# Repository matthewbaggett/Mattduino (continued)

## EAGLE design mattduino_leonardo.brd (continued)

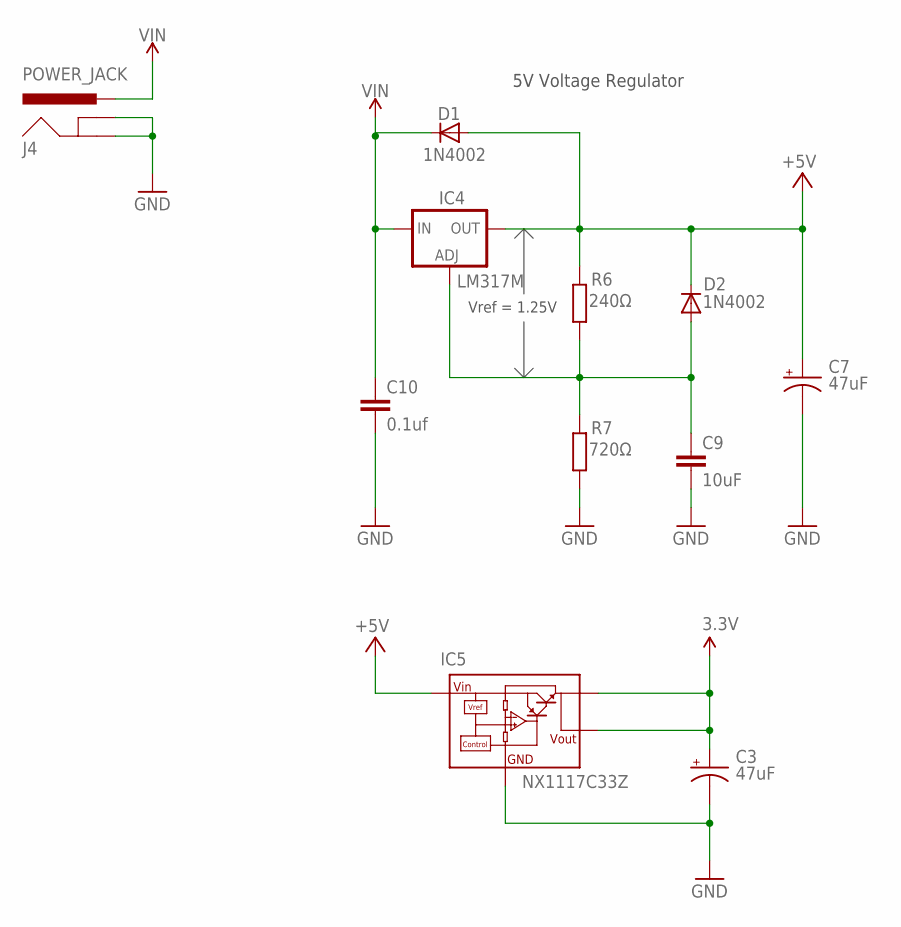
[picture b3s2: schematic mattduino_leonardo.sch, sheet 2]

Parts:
C3, C7: 47uF; PANASONIC_D
C9: 10uF; C1206
C10: 0.1uf; C1206
D1, D2: 1N4002; SOD-123
IC4: LM317MBSTT3; SOT223; PARTNUMBER LM317M
IC5: NX1117C33Z; SOT223
J4: POWER_JACK; POWER_JACK_PTH
R6: 240Ω; R1206
R7: 720Ω; R1206

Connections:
3.3V: C3.+, IC5.2 (VOUT1), IC5.4 (VOUT); also elsewhere on the board
+5V: C7.+, D1.A, D2.C, IC4.4 (OUT), IC5.3 (VIN), R6.2; also elsewhere on the board
GND: C3.-, C7.-, C9.2, C10.2, IC5.1 (GND), J4.GND, J4.GNDBREAK, R7.1; also elsewhere on the board
unnamed: C9.1, D2.A, IC4.1 (ADJ), R6.1, R7.2
VIN: C10.1, D1.C, IC4.3 (IN), J4.PWR; also elsewhere on the board

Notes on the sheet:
5V Voltage Regulator
Vref = 1.25V

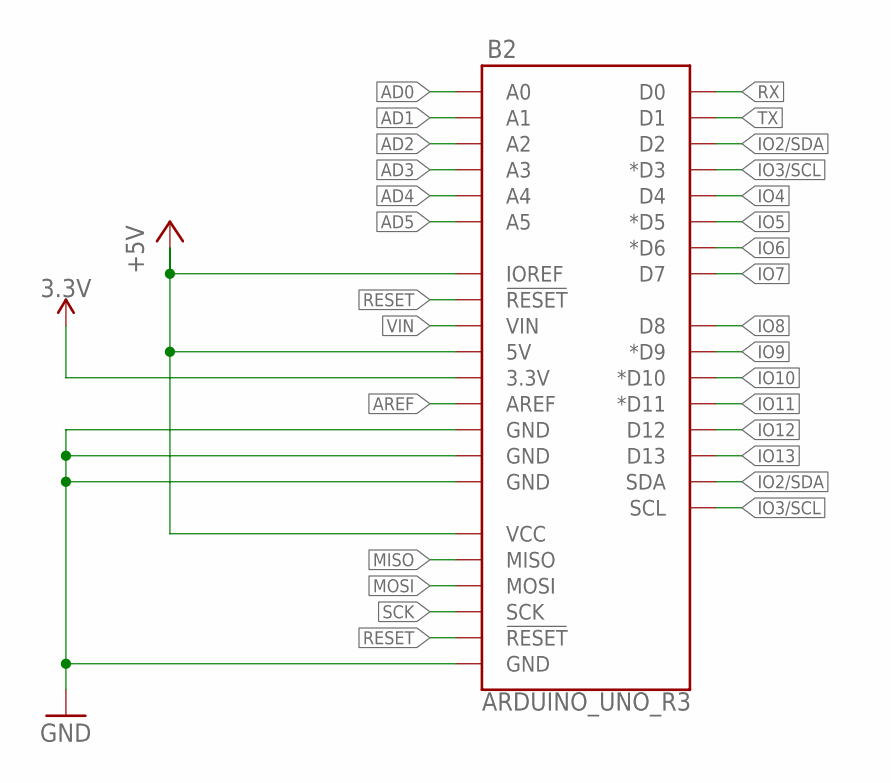
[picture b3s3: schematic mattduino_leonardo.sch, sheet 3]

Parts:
B2: ARDUINO_UNO_R3; ARDUINO_R3

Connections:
3.3V: B2.3.3V; also elsewhere on the board
+5V: B2.5V, B2.IOREF, B2.VCC; also elsewhere on the board
AD0: B2.A0; also elsewhere on the board
AD1: B2.A1; also elsewhere on the board
AD2: B2.A2; also elsewhere on the board
AD3: B2.A3; also elsewhere on the board
AD4: B2.A4; also elsewhere on the board
AD5: B2.A5; also elsewhere on the board
AREF: B2.AREF; also elsewhere on the board
GND: B2.GND@1 (GND), B2.GND@2 (GND), B2.GND@3 (GND), B2.GND@4 (GND); also elsewhere on the board
IO2/SDA: B2.D2, B2.SDA; also elsewhere on the board
IO3/SCL: B2.D3 (*D3), B2.SCL; also elsewhere on the board
IO4: B2.D4; also elsewhere on the board
IO5: B2.D5 (*D5); also elsewhere on the board
IO6: B2.D6 (*D6); also elsewhere on the board
IO7: B2.D7; also elsewhere on the board
IO8: B2.D8; also elsewhere on the board
IO9: B2.D9 (*D9); also elsewhere on the board
IO10: B2.D10 (*D10); also elsewhere on the board
IO11: B2.D11 (*D11); also elsewhere on the board
IO12: B2.D12; also elsewhere on the board
IO13: B2.D13; also elsewhere on the board
MISO: B2.MISO; also elsewhere on the board
MOSI: B2.MOSI; also elsewhere on the board
RESET: B2.RESET@1 (!RESET!), B2.RESET@2 (!RESET!); also elsewhere on the board
RX: B2.D0; also elsewhere on the board
SCK: B2.SCK; also elsewhere on the board
TX: B2.D1; also elsewhere on the board
VIN: B2.VIN; also elsewhere on the board

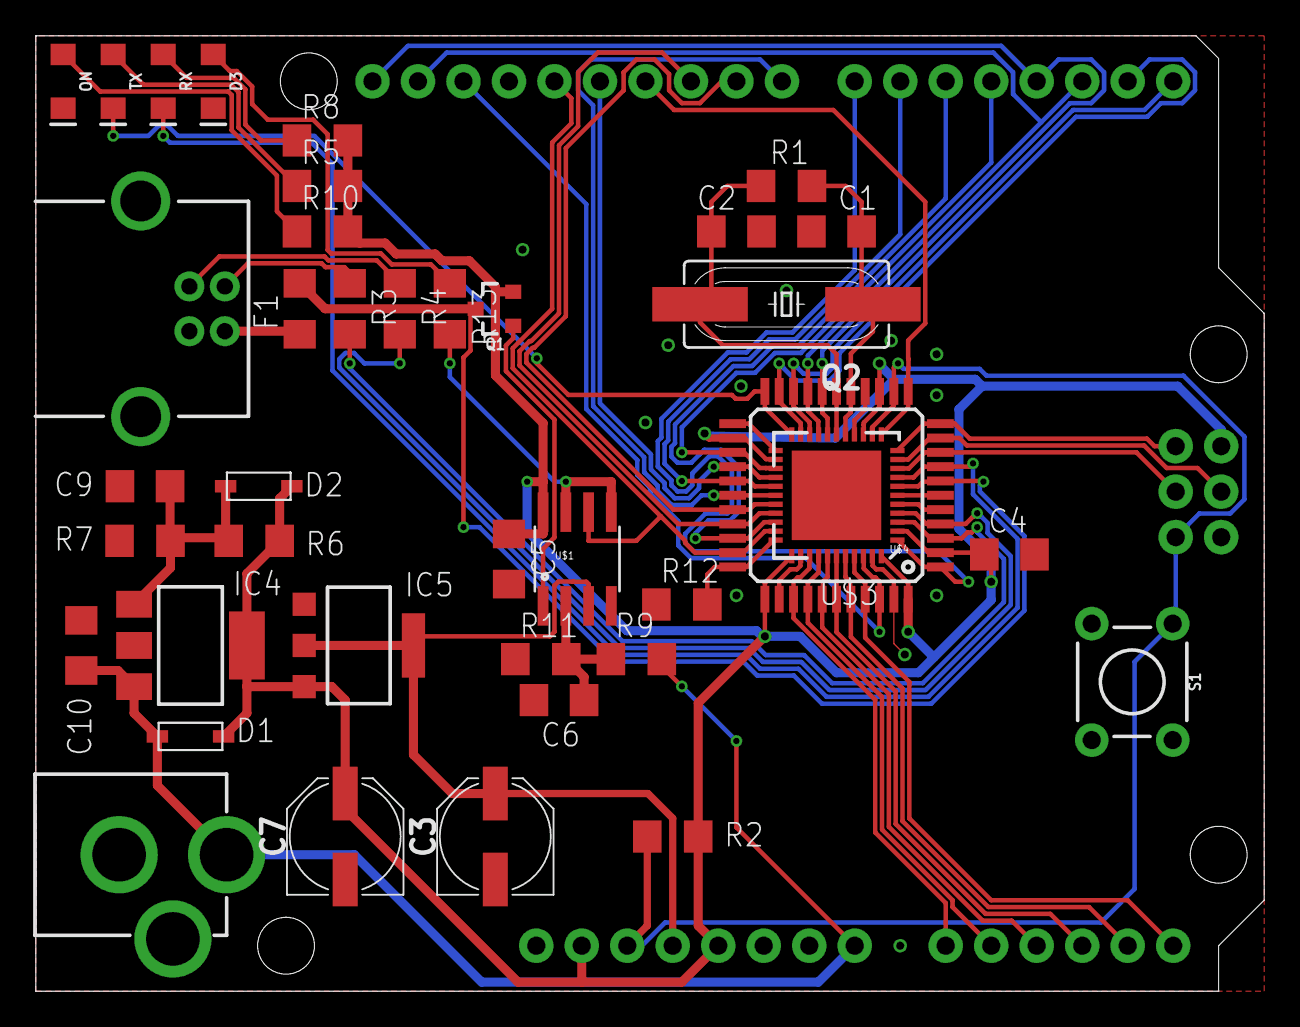
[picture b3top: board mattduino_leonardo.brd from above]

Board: 2 copper layers, 68.6 x 53.3 mm, 40 parts (0 on the bottom side), 48 nets.

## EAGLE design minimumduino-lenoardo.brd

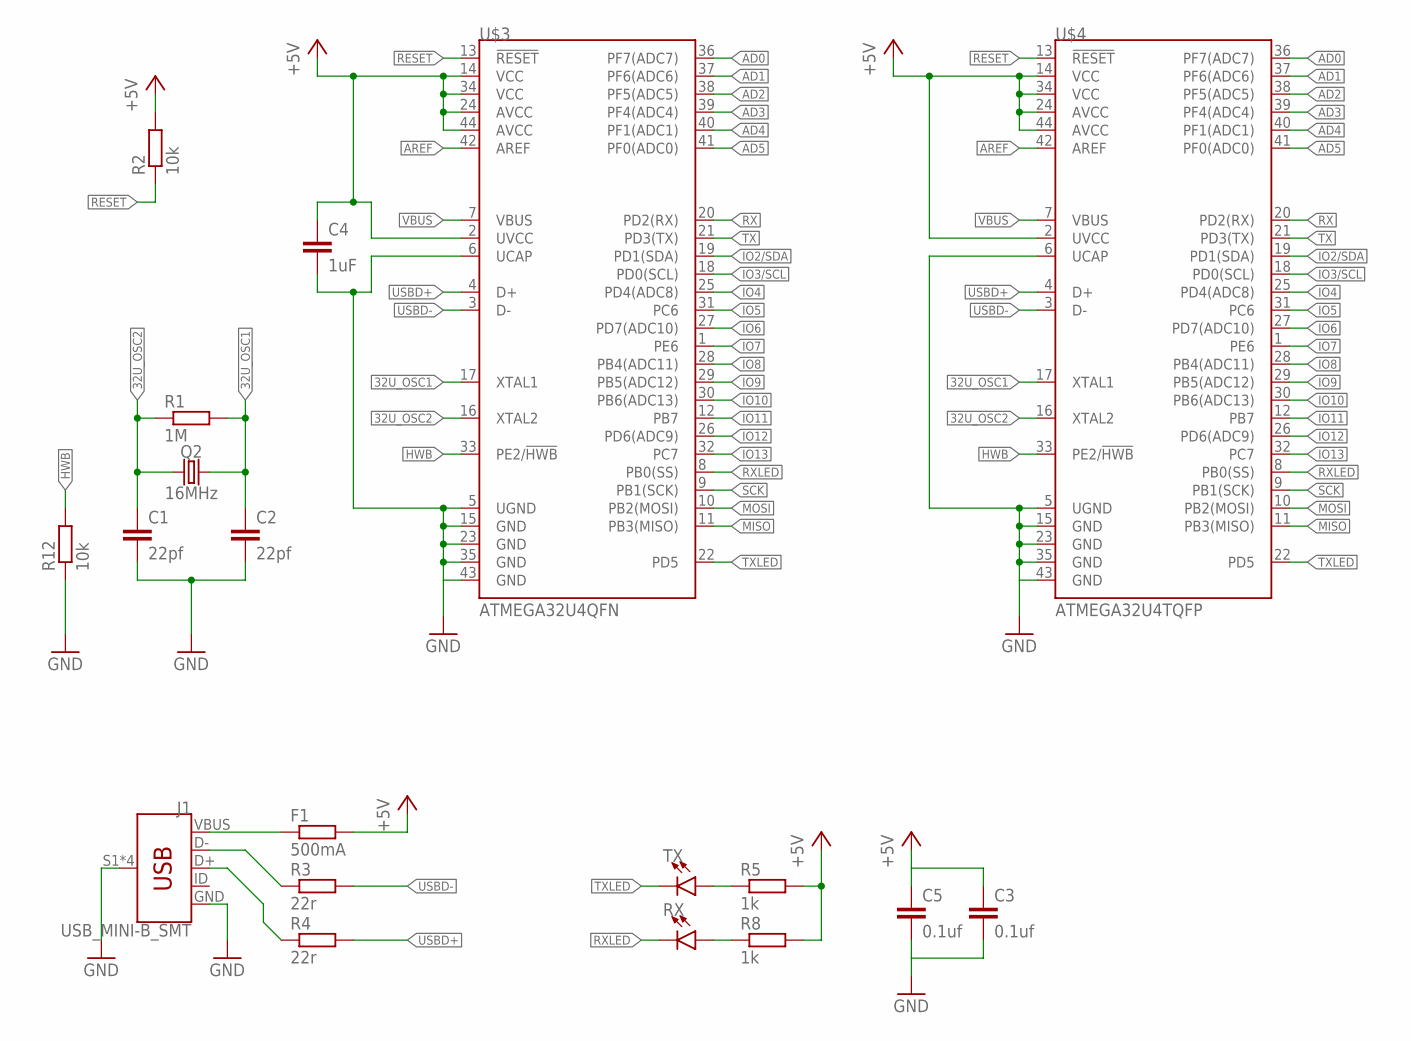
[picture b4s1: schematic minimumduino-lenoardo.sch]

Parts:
C1, C2: 22pf; C0805
C3, C5: 0.1uf; C0805
C4: 1uF; C0805
F1: 500mA; R1206
J1: USB_MINI-B_SMT; USB-MINIB
Q2: 16MHz; CRYSTAL-SMD-5X3.2-4PAD
R1: 1M; R0805
R2, R12: 10k; R0805
R3, R4: 22r; R0805
R5, R8: 1k; R0805
RX: LED1206; LED-1206
TX: LED1206; LED-1206
U$3: ATMEGA32U4QFN; SPARKFUN-DIGITALIC_QFN-44
U$4: ATMEGA32U4TQFP; SPARKFUN-DIGITALIC_TQFP44

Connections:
32U_OSC1: C2.1, Q2.3 (2), R1.2, U$3.17 (XTAL1), U$4.17 (XTAL1)
32U_OSC2: C1.1, Q2.1, R1.1, U$3.16 (XTAL2), U$4.16 (XTAL2)
+5V: C3.1, C4.1, C5.1, F1.2, R2.2, R5.2, R8.2, U$3.2 (UVCC), U$3.14 (VCC), U$3.24 (AVCC), U$3.34 (VCC), U$3.44 (AVCC), U$4.2 (UVCC), U$4.14 (VCC), U$4.24 (AVCC), U$4.34 (VCC), U$4.44 (AVCC)
AD0: U$3.36 (PF7(ADC7)), U$4.36 (PF7(ADC7))
AD1: U$3.37 (PF6(ADC6)), U$4.37 (PF6(ADC6))
AD2: U$3.38 (PF5(ADC5)), U$4.38 (PF5(ADC5))
AD3: U$3.39 (PF4(ADC4)), U$4.39 (PF4(ADC4))
AD4: U$3.40 (PF1(ADC1)), U$4.40 (PF1(ADC1))
AD5: U$3.41 (PF0(ADC0)), U$4.41 (PF0(ADC0))
AREF: U$3.42 (AREF), U$4.42 (AREF)
GND: C1.2, C2.2, C3.2, C4.2, C5.2, J1.GND, J1.S1 (SHIELD), J1.S2 (SHIELD), J1.S3 (SHIELD), J1.S4 (SHIELD), R12.1, U$3.5 (UGND), U$3.6 (UCAP), U$3.15 (GND), U$3.23 (GND), U$3.35 (GND), U$3.43 (GND), U$4.5 (UGND), U$4.6 (UCAP), U$4.15 (GND), U$4.23 (GND), U$4.35 (GND), U$4.43 (GND)
HWB: R12.2, U$3.33 (PE2/!HWB), U$4.33 (PE2/!HWB)
IO2/SDA: U$3.19 (PD1(SDA)), U$4.19 (PD1(SDA))
IO3/SCL: U$3.18 (PD0(SCL)), U$4.18 (PD0(SCL))
IO4: U$3.25 (PD4(ADC8)), U$4.25 (PD4(ADC8))
IO5: U$3.31 (PC6), U$4.31 (PC6)
IO6: U$3.27 (PD7(ADC10)), U$4.27 (PD7(ADC10))
IO7: U$3.1 (PE6), U$4.1 (PE6)
IO8: U$3.28 (PB4(ADC11)), U$4.28 (PB4(ADC11))
IO9: U$3.29 (PB5(ADC12)), U$4.29 (PB5(ADC12))
IO10: U$3.30 (PB6(ADC13)), U$4.30 (PB6(ADC13))
IO11: U$3.12 (PB7), U$4.12 (PB7)
IO12: U$3.26 (PD6(ADC9)), U$4.26 (PD6(ADC9))
IO13: U$3.32 (PC7), U$4.32 (PC7)
MISO: U$3.11 (PB3(MISO)), U$4.11 (PB3(MISO))
MOSI: U$3.10 (PB2(MOSI)), U$4.10 (PB2(MOSI))
unnamed: R8.1, RX.A
unnamed: R5.1, TX.A
RESET: R2.1, U$3.13 (!RESET), U$4.13 (!RESET)
RX: U$3.20 (PD2(RX)), U$4.20 (PD2(RX))
RXLED: RX.C, U$3.8 (PB0(SS)), U$4.8 (PB0(SS))
SCK: U$3.9 (PB1(SCK)), U$4.9 (PB1(SCK))
TX: U$3.21 (PD3(TX)), U$4.21 (PD3(TX))
TXLED: TX.C, U$3.22 (PD5), U$4.22 (PD5)
USBD+: R4.2, U$3.4 (D+), U$4.4 (D+)
USBD-: R3.2, U$3.3 (D-), U$4.3 (D-)
USBR+: J1.D+, R4.1
USBR-: J1.D-, R3.1
VBUS: U$3.7 (VBUS), U$4.7 (VBUS)
VBUS_UNFUSED: F1.1, J1.VBUS

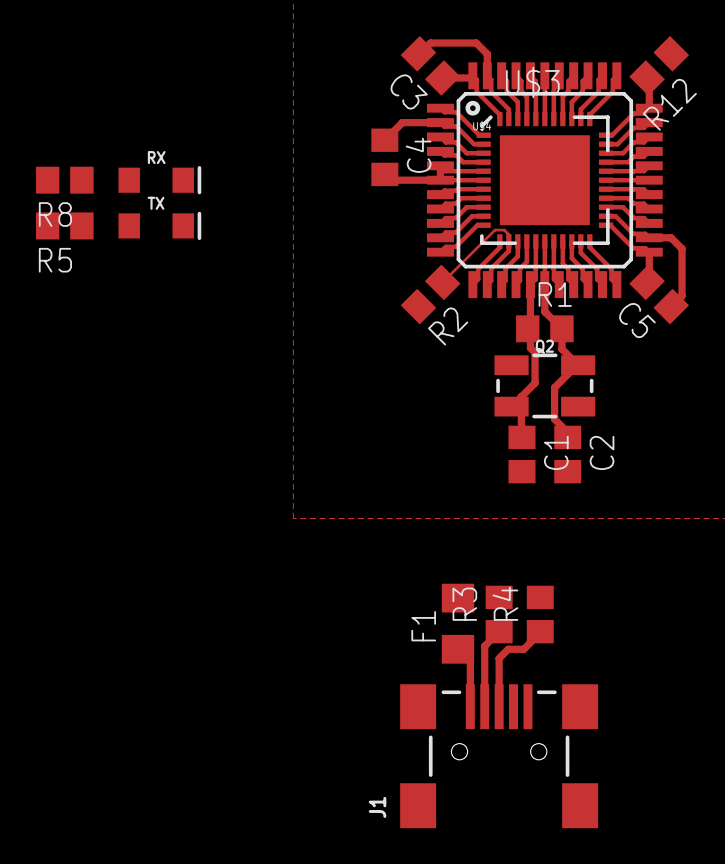
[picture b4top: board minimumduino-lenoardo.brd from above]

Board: 2 copper layers, 19 parts (0 on the bottom side), 40 nets.

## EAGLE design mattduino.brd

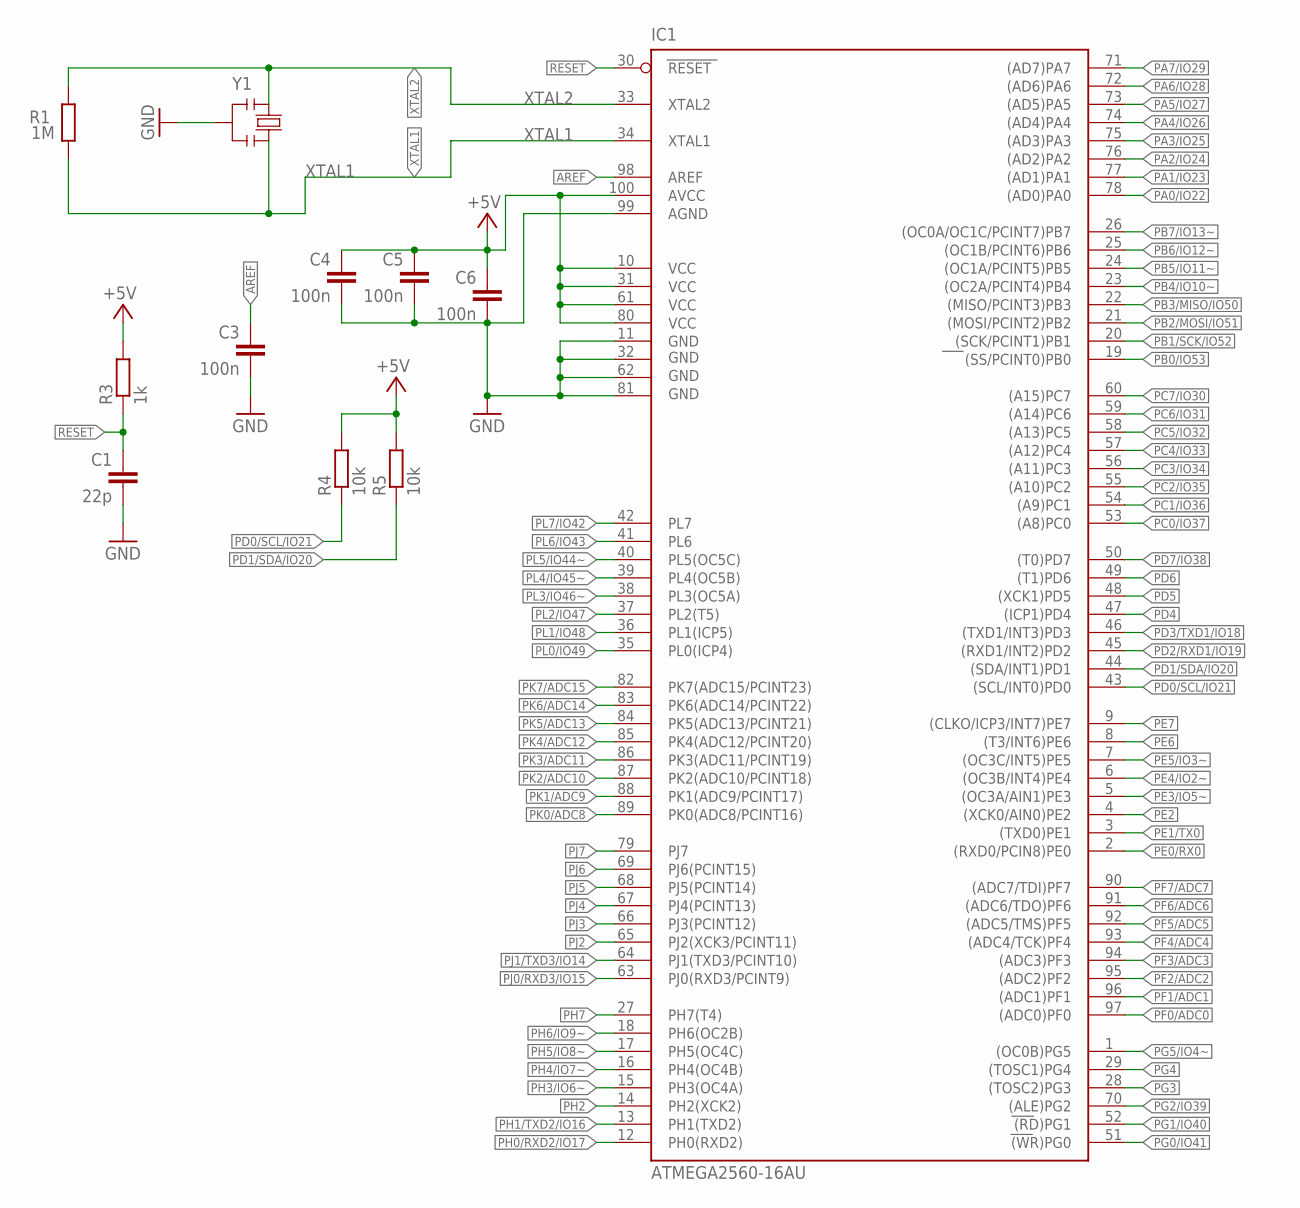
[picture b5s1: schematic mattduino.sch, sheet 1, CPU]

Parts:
C1: 22p; C1206
C3, C4, C5, C6: 100n; C1206
IC1: ATMEGA2560-16AU; TQFP100
R1: 1M; R1206
R3: 1k; R1206
R4, R5: 10k; R1206
Y1: CSTCE16M0V53-R0 16MHZ; RESONATOR

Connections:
+5V: C4.1, C5.1, C6.1, IC1.10 (VCC), IC1.31 (VCC1), IC1.61 (VCC2), IC1.80 (VCC3), IC1.100 (AVCC), R3.2, R4.2, R5.2; also elsewhere on the board
AREF: C3.1, IC1.98 (AREF); also elsewhere on the board
GND: C1.2, C3.2, C4.2, C5.2, C6.2, IC1.11 (GND), IC1.32 (GND1), IC1.62 (GND2), IC1.81 (GND3), IC1.99 (AGND), Y1.2; also elsewhere on the board
PA0/IO22: IC1.78 ((AD0)PA0); also elsewhere on the board
PA1/IO23: IC1.77 ((AD1)PA1); also elsewhere on the board
PA2/IO24: IC1.76 ((AD2)PA2); also elsewhere on the board
PA3/IO25: IC1.75 ((AD3)PA3); also elsewhere on the board
PA4/IO26: IC1.74 ((AD4)PA4); also elsewhere on the board
PA5/IO27: IC1.73 ((AD5)PA5); also elsewhere on the board
PA6/IO28: IC1.72 ((AD6)PA6); also elsewhere on the board
PA7/IO29: IC1.71 ((AD7)PA7); also elsewhere on the board
PB0/IO53: IC1.19 ((SS/PCINT0)PB0); also elsewhere on the board
PB1/SCK/IO52: IC1.20 ((SCK/PCINT1)PB1); also elsewhere on the board
PB2/MOSI/IO51: IC1.21 ((MOSI/PCINT2)PB2); also elsewhere on the board
PB3/MISO/IO50: IC1.22 ((MISO/PCINT3)PB3); also elsewhere on the board
PB4/IO10~: IC1.23 ((OC2A/PCINT4)PB4); also elsewhere on the board
PB5/IO11~: IC1.24 ((OC1A/PCINT5)PB5); also elsewhere on the board
PB6/IO12~: IC1.25 ((OC1B/PCINT6)PB6); also elsewhere on the board
PB7/IO13~: IC1.26 ((OC0A/OC1C/PCINT7)PB7); also elsewhere on the board
PC0/IO37: IC1.53 ((A8)PC0); also elsewhere on the board
PC1/IO36: IC1.54 ((A9)PC1); also elsewhere on the board
PC2/IO35: IC1.55 ((A10)PC2); also elsewhere on the board
PC3/IO34: IC1.56 ((A11)PC3); also elsewhere on the board
PC4/IO33: IC1.57 ((A12)PC4); also elsewhere on the board
PC5/IO32: IC1.58 ((A13)PC5); also elsewhere on the board
PC6/IO31: IC1.59 ((A14)PC6); also elsewhere on the board
PC7/IO30: IC1.60 ((A15)PC7); also elsewhere on the board
PD0/SCL/IO21: IC1.43 ((SCL/INT0)PD0), R4.1; also elsewhere on the board
PD1/SDA/IO20: IC1.44 ((SDA/INT1)PD1), R5.1; also elsewhere on the board
PD2/RXD1/IO19: IC1.45 ((RXD1/INT2)PD2); also elsewhere on the board
PD3/TXD1/IO18: IC1.46 ((TXD1/INT3)PD3); also elsewhere on the board
PD4: IC1.47 ((ICP1)PD4); also elsewhere on the board
PD5: IC1.48 ((XCK1)PD5); also elsewhere on the board
PD6: IC1.49 ((T1)PD6); also elsewhere on the board
PD7/IO38: IC1.50 ((T0)PD7); also elsewhere on the board
PE0/RX0: IC1.2 ((RXD0/PCIN8)PE0); also elsewhere on the board
PE1/TX0: IC1.3 ((TXD0)PE1); also elsewhere on the board
PE2: IC1.4 ((XCK0/AIN0)PE2); also elsewhere on the board
PE3/IO5~: IC1.5 ((OC3A/AIN1)PE3); also elsewhere on the board
PE4/IO2~: IC1.6 ((OC3B/INT4)PE4); also elsewhere on the board
PE5/IO3~: IC1.7 ((OC3C/INT5)PE5); also elsewhere on the board
PE6: IC1.8 ((T3/INT6)PE6); also elsewhere on the board
PE7: IC1.9 ((CLKO/ICP3/INT7)PE7); also elsewhere on the board
PF0/ADC0: IC1.97 ((ADC0)PF0); also elsewhere on the board
PF1/ADC1: IC1.96 ((ADC1)PF1); also elsewhere on the board
PF2/ADC2: IC1.95 ((ADC2)PF2); also elsewhere on the board
PF3/ADC3: IC1.94 ((ADC3)PF3); also elsewhere on the board
PF4/ADC4: IC1.93 ((ADC4/TCK)PF4); also elsewhere on the board
PF5/ADC5: IC1.92 ((ADC5/TMS)PF5); also elsewhere on the board
PF6/ADC6: IC1.91 ((ADC6/TDO)PF6); also elsewhere on the board
PF7/ADC7: IC1.90 ((ADC7/TDI)PF7); also elsewhere on the board
PG0/IO41: IC1.51 ((WR)PG0); also elsewhere on the board
PG1/IO40: IC1.52 ((RD)PG1); also elsewhere on the board
PG2/IO39: IC1.70 ((ALE)PG2); also elsewhere on the board
PG3: IC1.28 ((TOSC2)PG3); also elsewhere on the board
PG4: IC1.29 ((TOSC1)PG4); also elsewhere on the board
PG5/IO4~: IC1.1 ((OC0B)PG5); also elsewhere on the board
PH0/RXD2/IO17: IC1.12 (PH0(RXD2)); also elsewhere on the board
PH1/TXD2/IO16: IC1.13 (PH1(TXD2)); also elsewhere on the board
PH2: IC1.14 (PH2(XCK2)); also elsewhere on the board
PH3/IO6~: IC1.15 (PH3(OC4A)); also elsewhere on the board
PH4/IO7~: IC1.16 (PH4(OC4B)); also elsewhere on the board
PH5/IO8~: IC1.17 (PH5(OC4C)); also elsewhere on the board
PH6/IO9~: IC1.18 (PH6(OC2B)); also elsewhere on the board
PH7: IC1.27 (PH7(T4)); also elsewhere on the board
PJ0/RXD3/IO15: IC1.63 (PJ0(RXD3/PCINT9)); also elsewhere on the board
PJ1/TXD3/IO14: IC1.64 (PJ1(TXD3/PCINT10)); also elsewhere on the board
PJ2: IC1.65 (PJ2(XCK3/PCINT11)); also elsewhere on the board
PJ3: IC1.66 (PJ3(PCINT12)); also elsewhere on the board
PJ4: IC1.67 (PJ4(PCINT13)); also elsewhere on the board
PJ5: IC1.68 (PJ5(PCINT14)); also elsewhere on the board
PJ6: IC1.69 (PJ6(PCINT15)); also elsewhere on the board
PJ7: IC1.79 (PJ7); also elsewhere on the board
PK0/ADC8: IC1.89 (PK0(ADC8/PCINT16)); also elsewhere on the board
PK1/ADC9: IC1.88 (PK1(ADC9/PCINT17)); also elsewhere on the board
PK2/ADC10: IC1.87 (PK2(ADC10/PCINT18)); also elsewhere on the board
PK3/ADC11: IC1.86 (PK3(ADC11/PCINT19)); also elsewhere on the board
PK4/ADC12: IC1.85 (PK4(ADC12/PCINT20)); also elsewhere on the board
PK5/ADC13: IC1.84 (PK5(ADC13/PCINT21)); also elsewhere on the board
PK6/ADC14: IC1.83 (PK6(ADC14/PCINT22)); also elsewhere on the board
PK7/ADC15: IC1.82 (PK7(ADC15/PCINT23)); also elsewhere on the board
PL0/IO49: IC1.35 (PL0(ICP4)); also elsewhere on the board
PL1/IO48: IC1.36 (PL1(ICP5)); also elsewhere on the board
PL2/IO47: IC1.37 (PL2(T5)); also elsewhere on the board
PL3/IO46~: IC1.38 (PL3(OC5A)); also elsewhere on the board
PL4/IO45~: IC1.39 (PL4(OC5B)); also elsewhere on the board
PL5/IO44~: IC1.40 (PL5(OC5C)); also elsewhere on the board
PL6/IO43: IC1.41 (PL6); also elsewhere on the board
PL7/IO42: IC1.42 (PL7); also elsewhere on the board
RESET: C1.1, IC1.30 (RESET), R3.1; also elsewhere on the board
XTAL1: IC1.34 (XTAL1), R1.1, Y1.3
XTAL2: IC1.33 (XTAL2), R1.2, Y1.1

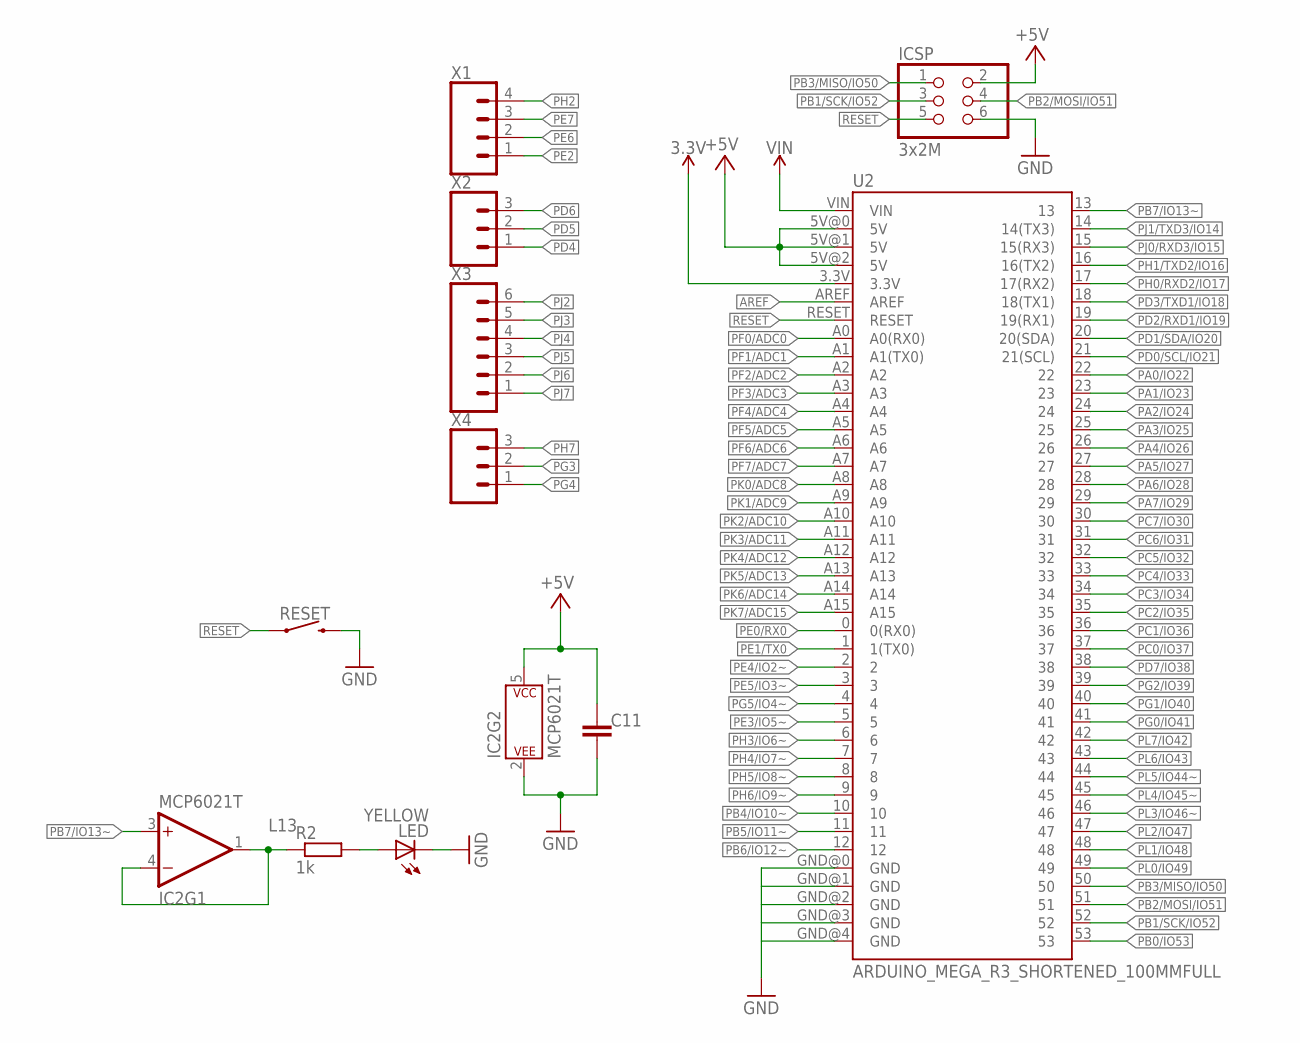
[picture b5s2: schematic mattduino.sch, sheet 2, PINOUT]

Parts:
C11: 100n; C1206
IC2: MCP6021T; SOT23-5
ICSP: 3x2M; 2X03
LED: YELLOW; CHIP-LED0805
R2: 1k; R1206
RESET: MOMENTARY-SWITCH-SPST-PTH-6.0MM; TACTILE_SWITCH_PTH_6.0MM
U2: ARDUINO_MEGA_R3_SHORTENED_100MMFULL; ARDUINO_MEGA_SHORTENED_100MM
X1: CONN_04; 1X04
X2, X4: CONN_03; 1X03
X3: CONN_06SILK_FEMALE_PTH; 1X06

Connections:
3.3V: U2.3.3V; also elsewhere on the board
+5V: C11.2, IC2.5 (P$V+), ICSP.2, U2.5V@0 (5V), U2.5V@1 (5V), U2.5V@2 (5V); also elsewhere on the board
AREF: U2.AREF; also elsewhere on the board
GND: C11.1, IC2.2 (P$V-), ICSP.6, LED.C, RESET.3 (2), U2.GND@0 (GND), U2.GND@1 (GND), U2.GND@2 (GND), U2.GND@3 (GND), U2.GND@4 (GND); also elsewhere on the board
L13: IC2.1 (OUT), IC2.4 (-IN), R2.1
unnamed: LED.A, R2.2
PA0/IO22: U2.22; also elsewhere on the board
PA1/IO23: U2.23; also elsewhere on the board
PA2/IO24: U2.24; also elsewhere on the board
PA3/IO25: U2.25; also elsewhere on the board
PA4/IO26: U2.26; also elsewhere on the board
PA5/IO27: U2.27; also elsewhere on the board
PA6/IO28: U2.28; also elsewhere on the board
PA7/IO29: U2.29; also elsewhere on the board
PB0/IO53: U2.53; also elsewhere on the board
PB1/SCK/IO52: ICSP.3, U2.52; also elsewhere on the board
PB2/MOSI/IO51: ICSP.4, U2.51; also elsewhere on the board
PB3/MISO/IO50: ICSP.1, U2.50; also elsewhere on the board
PB4/IO10~: U2.10; also elsewhere on the board
PB5/IO11~: U2.11; also elsewhere on the board
PB6/IO12~: U2.12; also elsewhere on the board
PB7/IO13~: IC2.3 (+IN), U2.13; also elsewhere on the board
PC0/IO37: U2.37; also elsewhere on the board
PC1/IO36: U2.36; also elsewhere on the board
PC2/IO35: U2.35; also elsewhere on the board
PC3/IO34: U2.34; also elsewhere on the board
PC4/IO33: U2.33; also elsewhere on the board
PC5/IO32: U2.32; also elsewhere on the board
PC6/IO31: U2.31; also elsewhere on the board
PC7/IO30: U2.30; also elsewhere on the board
PD0/SCL/IO21: U2.21 (21(SCL)); also elsewhere on the board
PD1/SDA/IO20: U2.20 (20(SDA)); also elsewhere on the board
PD2/RXD1/IO19: U2.19 (19(RX1)); also elsewhere on the board
PD3/TXD1/IO18: U2.18 (18(TX1)); also elsewhere on the board
PD4: X2.1; also elsewhere on the board
PD5: X2.2; also elsewhere on the board
PD6: X2.3; also elsewhere on the board
PD7/IO38: U2.38; also elsewhere on the board
PE0/RX0: U2.0 (0(RX0)); also elsewhere on the board
PE1/TX0: U2.1 (1(TX0)); also elsewhere on the board
PE2: X1.1; also elsewhere on the board
PE3/IO5~: U2.5; also elsewhere on the board
PE4/IO2~: U2.2; also elsewhere on the board
PE5/IO3~: U2.3; also elsewhere on the board
PE6: X1.2; also elsewhere on the board
PE7: X1.3; also elsewhere on the board
PF0/ADC0: U2.A0 (A0(RX0)); also elsewhere on the board
PF1/ADC1: U2.A1 (A1(TX0)); also elsewhere on the board
PF2/ADC2: U2.A2; also elsewhere on the board
PF3/ADC3: U2.A3; also elsewhere on the board
PF4/ADC4: U2.A4; also elsewhere on the board
PF5/ADC5: U2.A5; also elsewhere on the board
PF6/ADC6: U2.A6; also elsewhere on the board
PF7/ADC7: U2.A7; also elsewhere on the board
PG0/IO41: U2.41; also elsewhere on the board
PG1/IO40: U2.40; also elsewhere on the board
PG2/IO39: U2.39; also elsewhere on the board
PG3: X4.2; also elsewhere on the board
PG4: X4.1; also elsewhere on the board
PG5/IO4~: U2.4; also elsewhere on the board
PH0/RXD2/IO17: U2.17 (17(RX2)); also elsewhere on the board
PH1/TXD2/IO16: U2.16 (16(TX2)); also elsewhere on the board
PH2: X1.4; also elsewhere on the board
PH3/IO6~: U2.6; also elsewhere on the board
PH4/IO7~: U2.7; also elsewhere on the board
PH5/IO8~: U2.8; also elsewhere on the board
PH6/IO9~: U2.9; also elsewhere on the board
PH7: X4.3; also elsewhere on the board
PJ0/RXD3/IO15: U2.15 (15(RX3)); also elsewhere on the board
PJ1/TXD3/IO14: U2.14 (14(TX3)); also elsewhere on the board
PJ2: X3.6; also elsewhere on the board
PJ3: X3.5; also elsewhere on the board
PJ4: X3.4; also elsewhere on the board
PJ5: X3.3; also elsewhere on the board
PJ6: X3.2; also elsewhere on the board
PJ7: X3.1; also elsewhere on the board
PK0/ADC8: U2.A8; also elsewhere on the board
PK1/ADC9: U2.A9; also elsewhere on the board
PK2/ADC10: U2.A10; also elsewhere on the board
PK3/ADC11: U2.A11; also elsewhere on the board
PK4/ADC12: U2.A12; also elsewhere on the board
PK5/ADC13: U2.A13; also elsewhere on the board
PK6/ADC14: U2.A14; also elsewhere on the board
PK7/ADC15: U2.A15; also elsewhere on the board
PL0/IO49: U2.49; also elsewhere on the board
PL1/IO48: U2.48; also elsewhere on the board
PL2/IO47: U2.47; also elsewhere on the board
PL3/IO46~: U2.46; also elsewhere on the board
PL4/IO45~: U2.45; also elsewhere on the board
PL5/IO44~: U2.44; also elsewhere on the board
PL6/IO43: U2.43; also elsewhere on the board
PL7/IO42: U2.42; also elsewhere on the board
RESET: ICSP.5, RESET.1, U2.RESET; also elsewhere on the board
VIN: U2.VIN; also elsewhere on the board

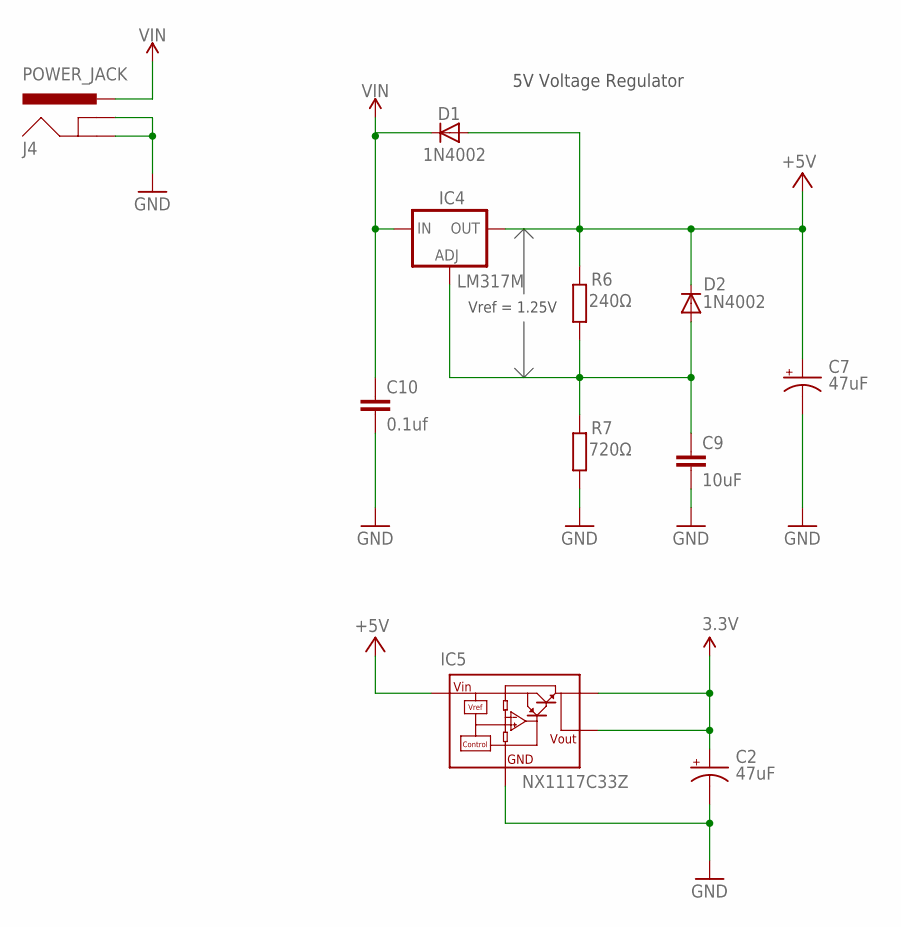
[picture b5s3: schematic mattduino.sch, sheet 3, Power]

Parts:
C2, C7: 47uF; PANASONIC_D
C9: 10uF; C1206
C10: 0.1uf; C1206
D1, D2: 1N4002; SOD-123
IC4: LM317MBSTT3; SOT223; PARTNUMBER LM317M
IC5: NX1117C33Z; SOT223
J4: POWER_JACK; POWER_JACK_PTH
R6: 240Ω; R1206
R7: 720Ω; R1206

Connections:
3.3V: C2.+, IC5.2 (VOUT1), IC5.4 (VOUT); also elsewhere on the board
+5V: C7.+, D1.A, D2.C, IC4.4 (OUT), IC5.3 (VIN), R6.2; also elsewhere on the board
GND: C2.-, C7.-, C9.2, C10.2, IC5.1 (GND), J4.GND, J4.GNDBREAK, R7.1; also elsewhere on the board
unnamed: C9.1, D2.A, IC4.1 (ADJ), R6.1, R7.2
VIN: C10.1, D1.C, IC4.3 (IN), J4.PWR; also elsewhere on the board

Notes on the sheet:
5V Voltage Regulator
Vref = 1.25V

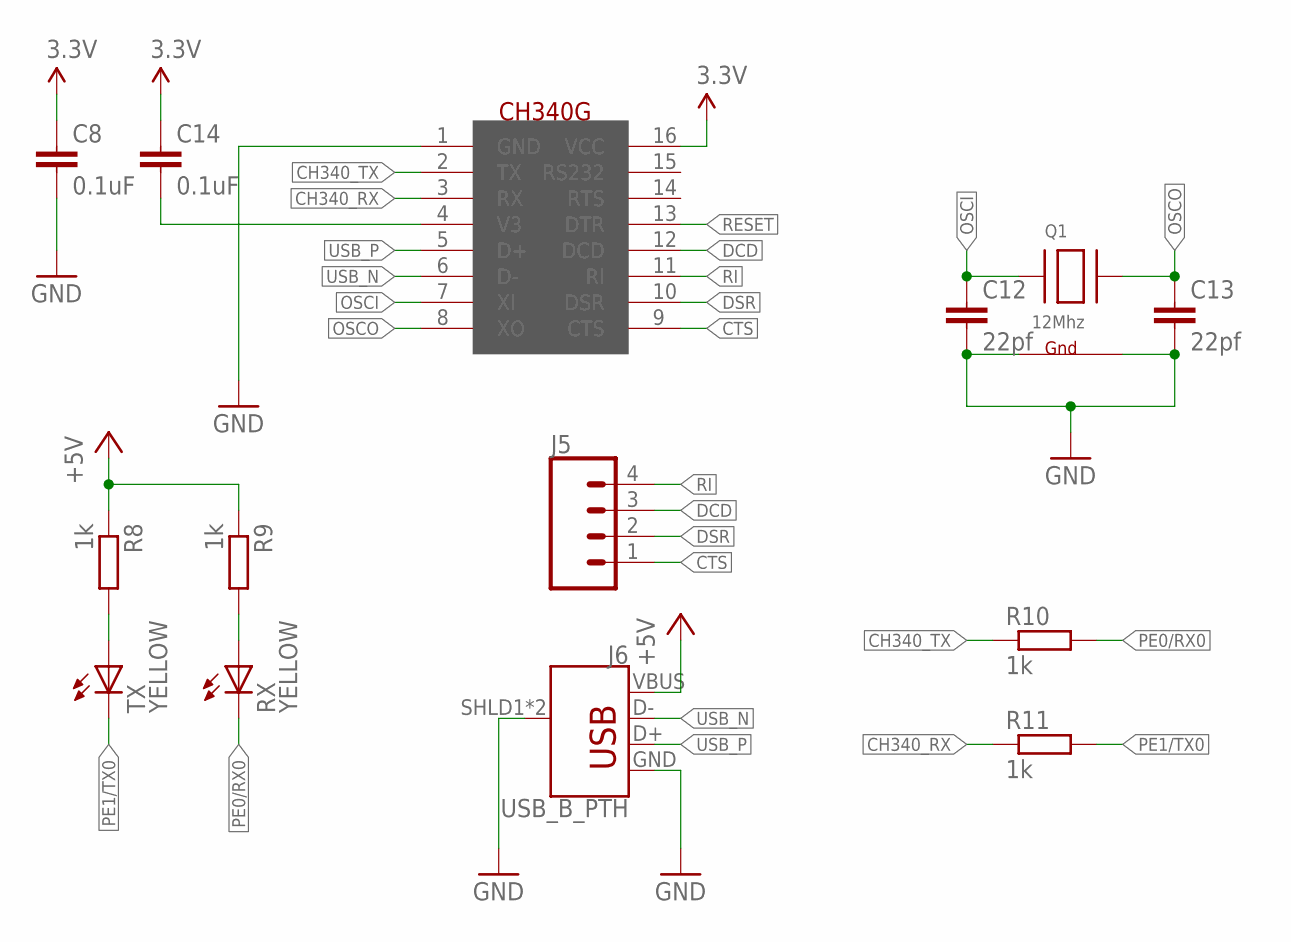
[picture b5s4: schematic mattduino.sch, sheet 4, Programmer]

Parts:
C8, C14: 0.1uF; C1206
C12, C13: 22pf; C1206
IC3: CH340G; SOIC16
J5: CONN_04; 1X04
J6: USB_B_PTH; USB-B-PTH
Q1: 12Mhz; NX3225
R8, R9, R10, R11: 1k; R1206
RX: YELLOW; CHIP-LED0805
TX: YELLOW; CHIP-LED0805

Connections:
3.3V: C8.1, C14.1, IC3.16 (VCC); also elsewhere on the board
+5V: J6.VBUS, R8.1, R9.1; also elsewhere on the board
CH340_RX: IC3.3 (RX), R11.1
CH340_TX: IC3.2 (TX), R10.1
CTS: IC3.9 (CTS), J5.1
DCD: IC3.12 (DCD), J5.3
DSR: IC3.10 (DSR), J5.2
GND: C8.2, C12.2, C13.2, IC3.1 (GND), J6.GND, J6.SHLD1 (SHIELD), J6.SHLD2 (SHIELD), Q1.2 (G2), Q1.4 (G1); also elsewhere on the board
unnamed: C14.2, IC3.4 (V3)
unnamed: R8.2, TX.A
unnamed: R9.2, RX.A
OSCI: C12.1, IC3.7 (XI), Q1.1 (X1)
OSCO: C13.1, IC3.8 (XO), Q1.3 (X2)
PE0/RX0: R10.2, RX.C; also elsewhere on the board
PE1/TX0: R11.2, TX.C; also elsewhere on the board
RESET: IC3.13 (DTR); also elsewhere on the board
RI: IC3.11 (RI), J5.4
USB_N: IC3.6 (D-), J6.D-
USB_P: IC3.5 (D+), J6.D+

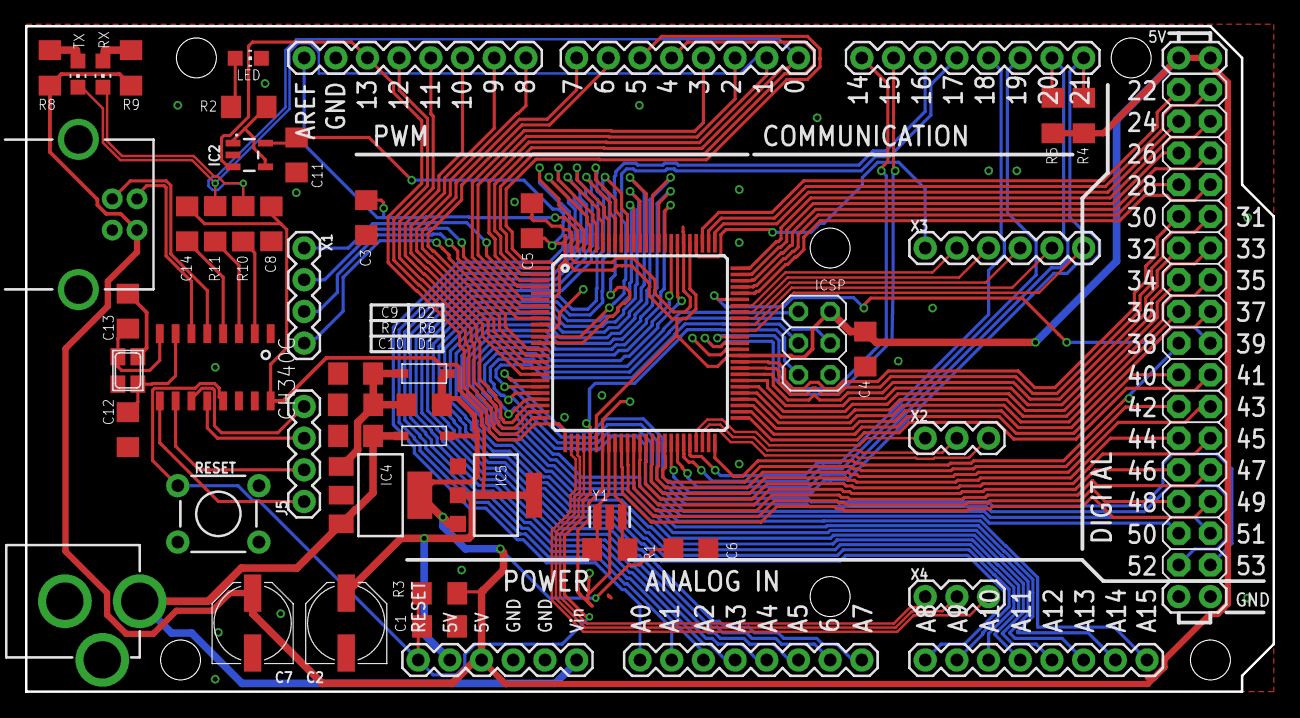
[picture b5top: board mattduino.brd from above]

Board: 2 copper layers, 100.0 x 53.3 mm, 47 parts (0 on the bottom side), 110 nets.

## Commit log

2018-02-08 Initial version of the Mattduino Mega.
2018-02-16 Move mattduino mega stuff into other files
2018-02-16 mattduino uno
2018-08-13 Apparently a bunch of changes I never committed
2018-08-13 Mattduino mega.. reall just a breakout for the ATMEL ATMEGA2560's TQFP100
2018-09-17 missing stuff
2018-09-17 updated eagle.epf
